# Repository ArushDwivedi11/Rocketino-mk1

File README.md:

# Rocketino-mk1
this is an arduino nano based data transmitting avionics PCB project for Rocketry High Power Rocketry Club BMSCE

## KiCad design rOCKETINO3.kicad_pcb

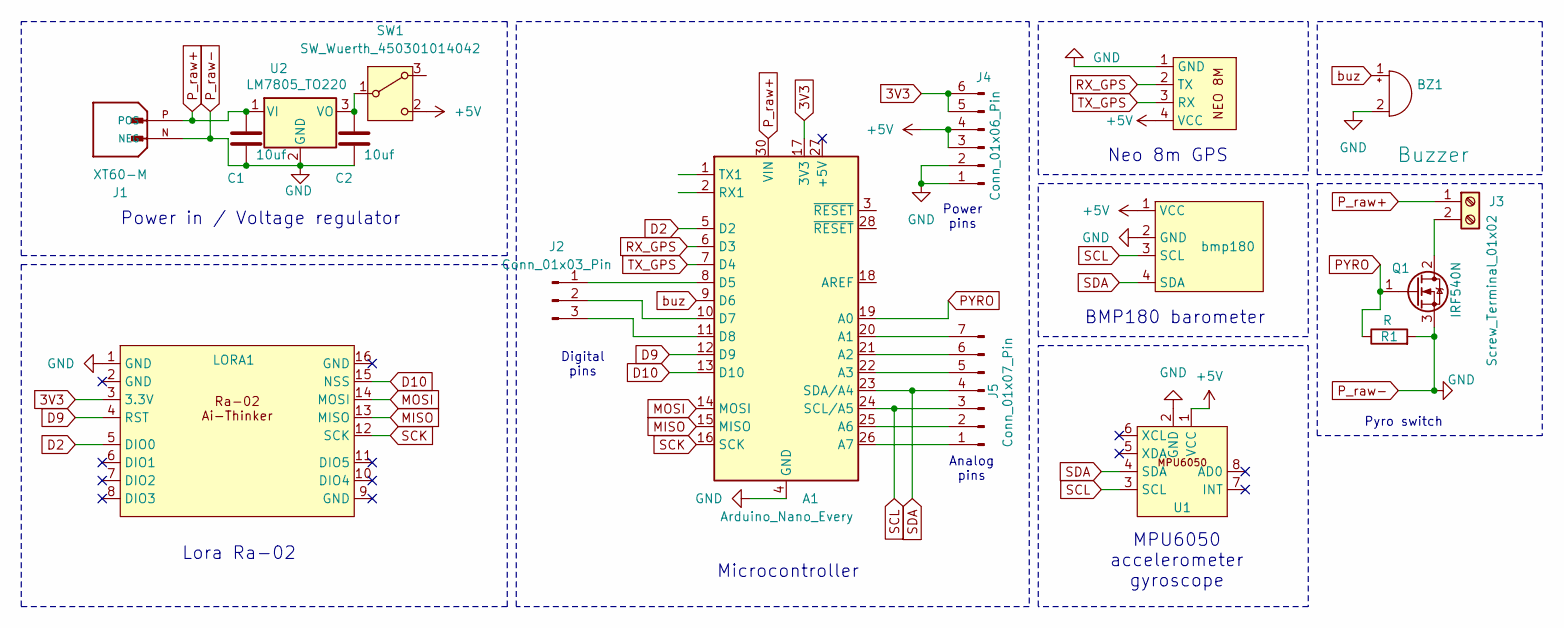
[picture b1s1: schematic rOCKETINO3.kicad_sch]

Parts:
A1: Arduino_Nano_Every; Arduino_Nano
BZ1: Buzzer; Buzzer_15x7.5RM7.6
C1, C2: 10uf; C_Disc_D5.0mm_W2.5mm_P2.50mm
J1: XT60-M; AMASS_XT60-M; PARTREV V1.2
J2: Conn_01x03_Pin; PinSocket_1x03_P2.54mm_Vertical
J3: Screw_Terminal_01x02; TerminalBlock_MaiXu_MX126-5.0-02P_1x02_P5.00mm
J4: Conn_01x06_Pin; PinSocket_1x06_P2.54mm_Vertical
J5: Conn_01x07_Pin; PinSocket_1x07_P2.54mm_Vertical
LORA1: Ra-02_module
Q1: IRF540N; TO-220-3_Vertical
R1: R; R_Axial_DIN0207_L6.3mm_D2.5mm_P7.62mm_Horizontal
SW1: SW_Wuerth_450301014042; SW_Slide-03_Wuerth-WS-SLTV_10x2.5x6.4_P2.54mm
U1: MPU6050
U2: LM7805_TO220; TO-220-3_Vertical
U4: AdafruitGPS
bmp180: BMP180

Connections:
3V3: A1.17 (3V3), J4.5, J4.6, LORA1.3 (3.3V)
+5V: J4.3, J4.4, SW1.2 (C), U1.1 (VCC), U4.4 (VCC), bmp180.1 (VCC)
D2: A1.5 (D2), LORA1.5 (DIO0)
D9: A1.12 (D9), LORA1.4 (RST)
D10: A1.13 (D10), LORA1.15 (NSS)
MISO: A1.15 (MISO), LORA1.13 (MISO)
MOSI: A1.14 (MOSI), LORA1.14 (MOSI)
unnamed: A1.20 (A1), J5.7
unnamed: A1.21 (A2), J5.6
unnamed: A1.22 (A3), J5.5
unnamed: A1.25 (A6), J5.2
unnamed: A1.26 (A7), J5.1
unnamed: A1.8 (D5), J2.1
unnamed: A1.10 (D7), J2.2
unnamed: A1.11 (D8), J2.3
unnamed: J3.2, Q1.2 (D)
unnamed: C2.1, SW1.1 (B), U2.3 (VO)
PYRO: A1.19 (A0), Q1.1 (G), R1.1
P_raw+: A1.30 (VIN), C1.1, J1.P (POS), J3.1, U2.1 (VI)
P_raw-: A1.4 (GND), A1.29 (GND), BZ1.2 (-), C1.2, C2.2, J1.N (NEG), J4.1, J4.2, LORA1.1 (GND), Q1.3 (S), R1.2, U1.2 (GND), U2.2 (GND), U4.1 (GND), bmp180.2 (GND)
RX_GPS: A1.6 (D3), U4.2 (TX)
SCK: A1.16 (SCK), LORA1.12 (SCK)
SCL: A1.24 (SCL/A5), J5.3, U1.3 (SCL), bmp180.3 (SCL)
SDA: A1.23 (SDA/A4), J5.4, U1.4 (SDA), bmp180.4 (SDA)
TX_GPS: A1.7 (D4), U4.3 (RX)
buz: A1.9 (D6), BZ1.1 (+)

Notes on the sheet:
Digital pins
Lora Ra-02
Neo 8m GPS
Pyro switch
Microcontroller
Power in / Voltage regulator
Power pins
MPU6050 accelerometer gyroscope
Analog pins
BMP180 barometer

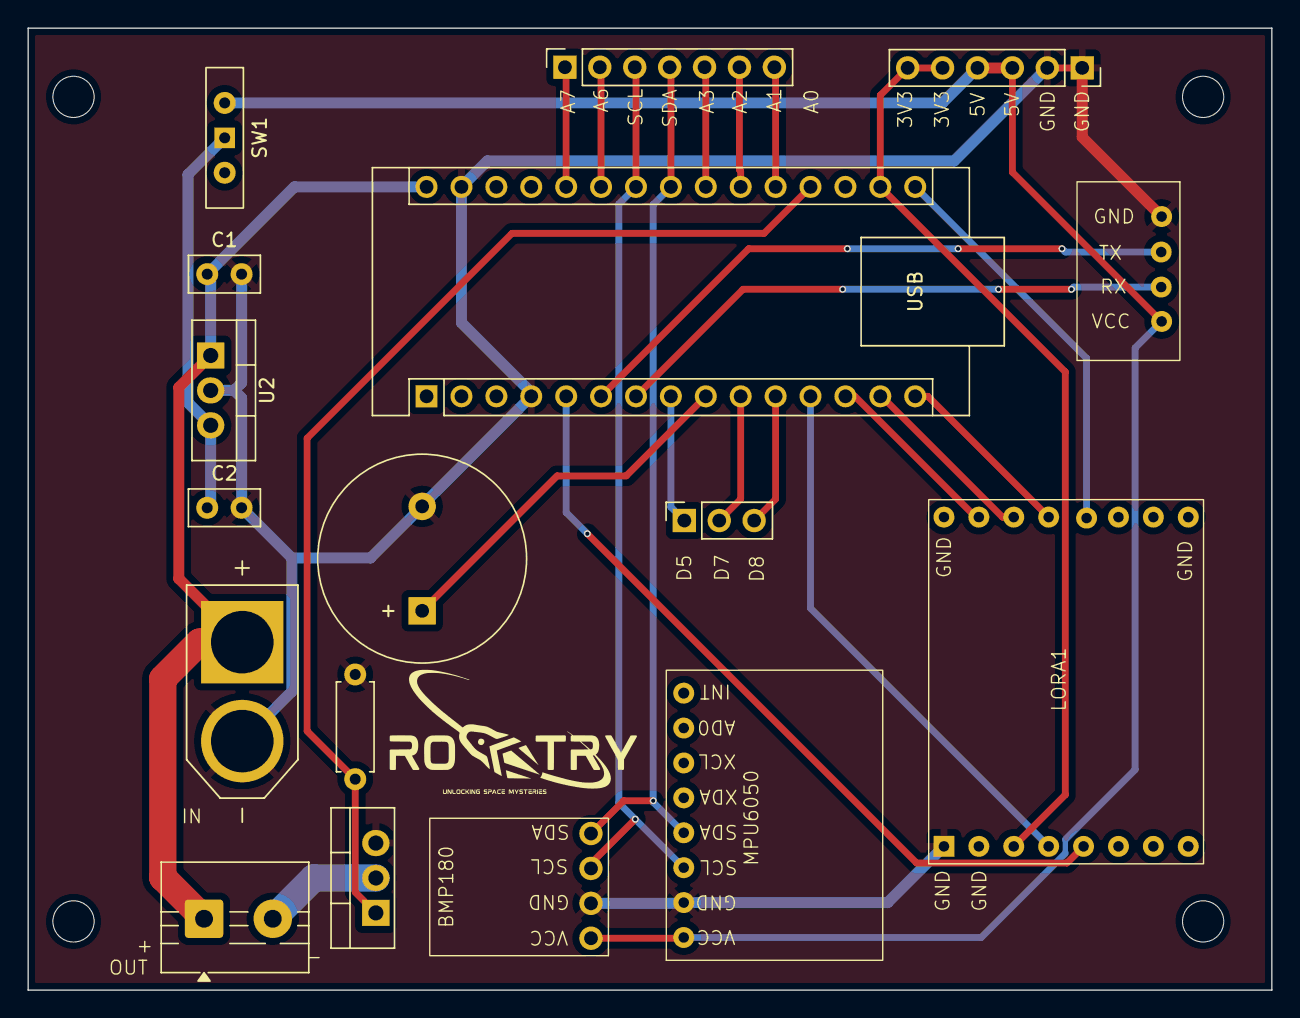
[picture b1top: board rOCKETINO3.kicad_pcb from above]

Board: 2 copper layers, 90.5 x 70.0 mm, 17 parts (0 on the bottom side), 26 nets.
